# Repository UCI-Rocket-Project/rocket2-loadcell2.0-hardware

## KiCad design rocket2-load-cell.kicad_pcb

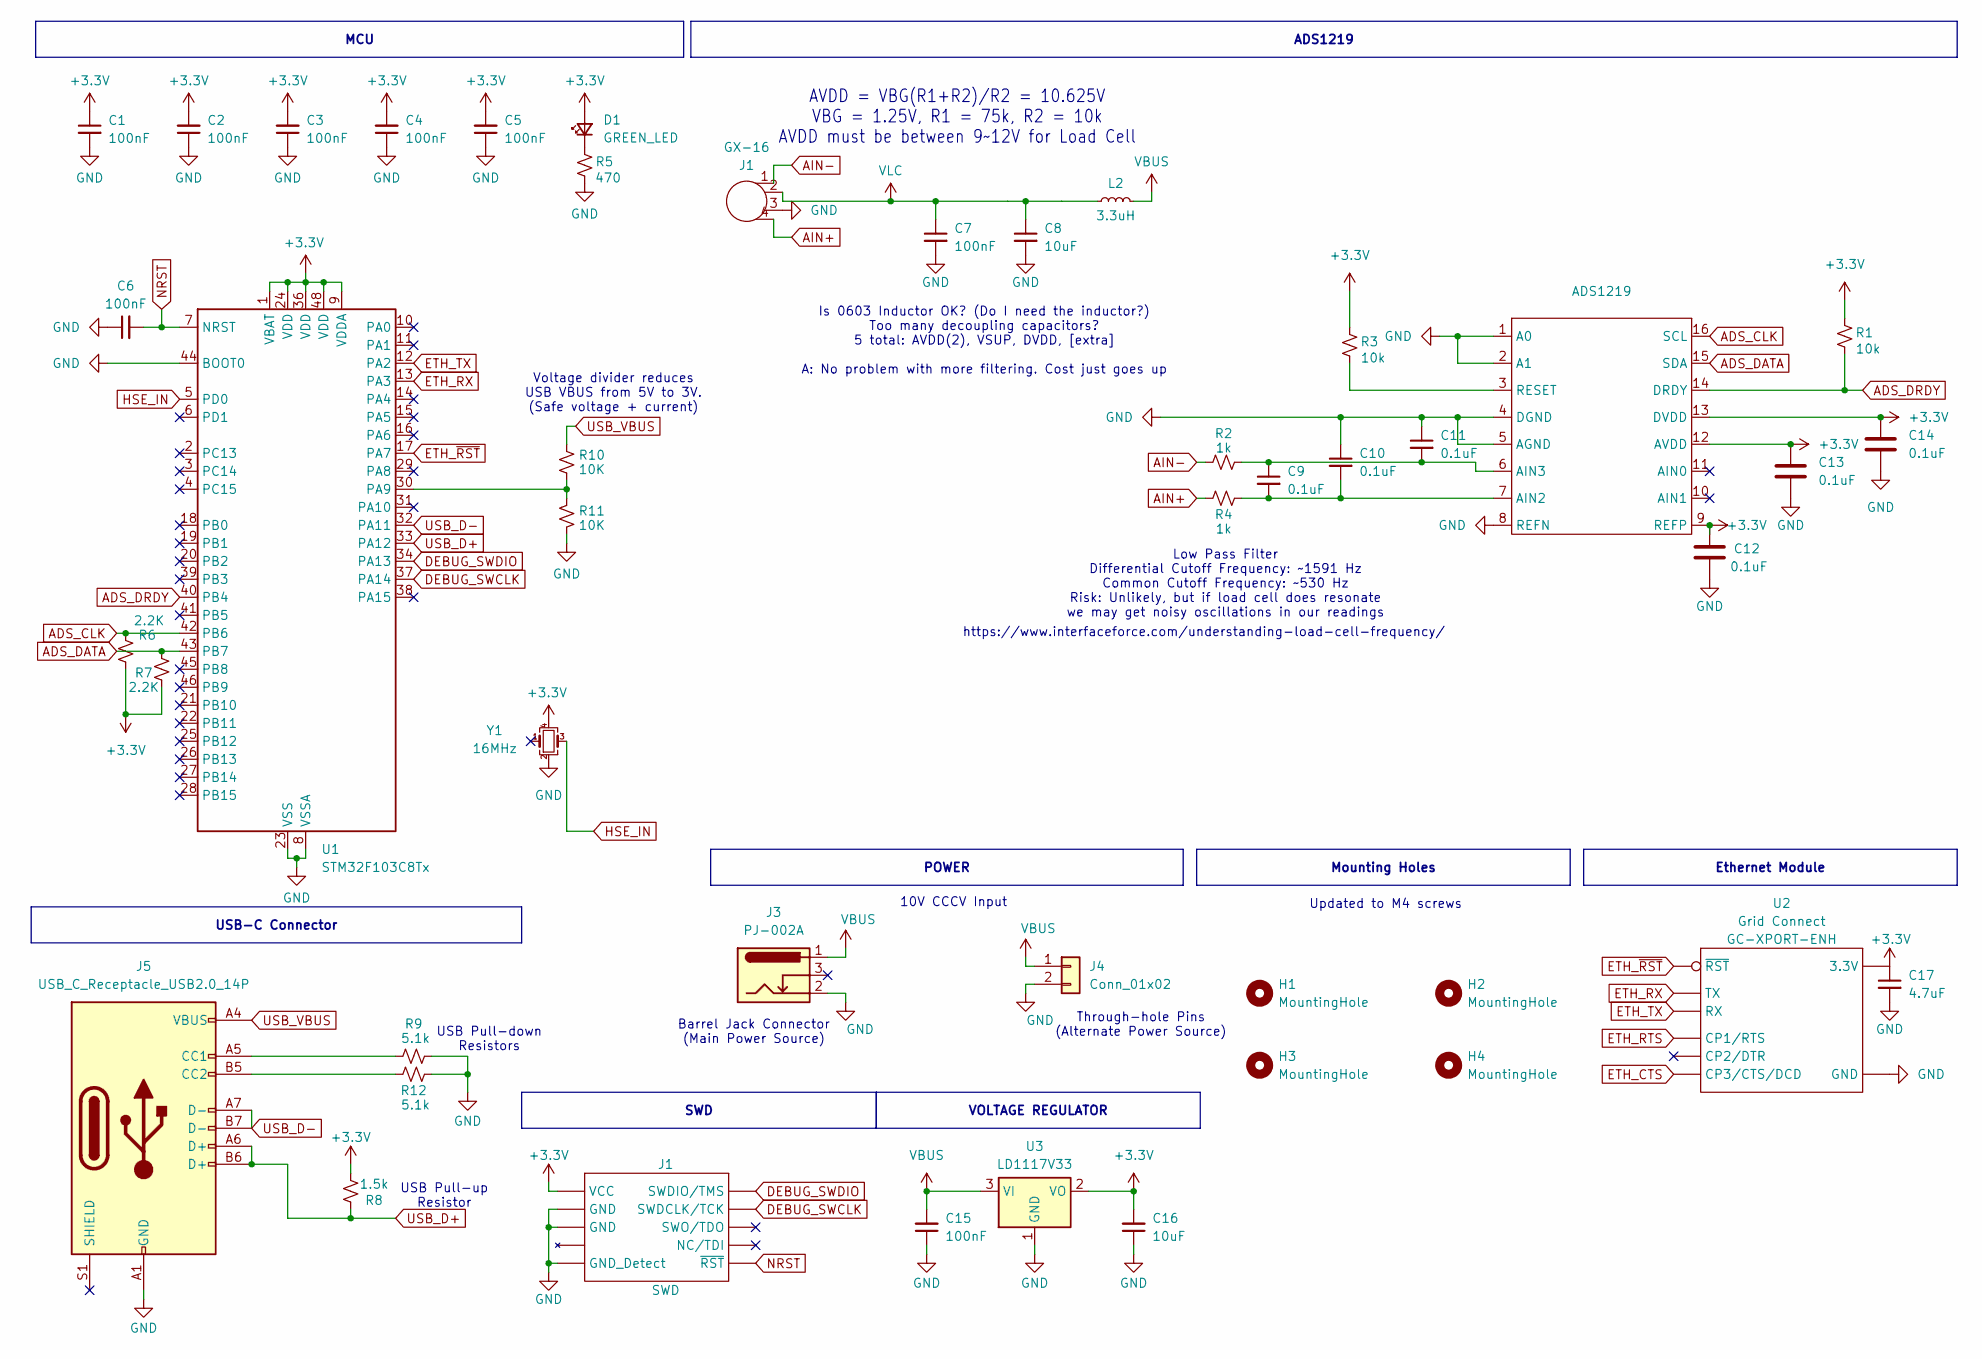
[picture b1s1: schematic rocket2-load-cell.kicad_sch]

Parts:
ADS1219: TSSOP-16_4.4x5mm_P0.65mm
C1, C2, C3, C4, C5, C6, C7, C15: 100nF; C_0603_1608Metric
C8, C16: 10uF; C_0603_1608Metric
C9, C10, C11, C14: 0.1uF; C_0603_1608Metric
C12, C13: 0.1uF; C_0603_1608Metric_Pad1.08x0.95mm_HandSolder
C17: 4.7uF; C_0603_1608Metric; Part # Generic 4.7uF 6.3V X7R 0603 MLCC
D1: GREEN_LED; LED_0603_1608Metric
GX-16: J1; GX16-4
H1, H2, H3, H4: MountingHole; MountingHole_4.3mm_M4_ISO7380_Pad
J1: SWD; PinHeader_2x05_P1.27mm_Vertical_SMD; Part # Generic 2x05 P1.27mm Vertical Pin Heade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
J3: PJ-002A; CUI_PJ-202A
J4: Conn_01x02
J5: USB_C_Receptacle_USB2.0_14P; USB_C_Receptacle_GCT_USB4110
L2: 3.3uH; L_0603_1608Metric
R1, R3: 10k; R_0603_1608Metric
R2, R4: 1k; R_0603_1608Metric
R5: 470; R_0603_1608Metric
R6, R7: 2.2K; R_0603_1608Metric
R8: 1.5k; R_0603_1608Metric
R9, R12: 5.1k; R_0603_1608Metric
R10, R11: 10K; R_0603_1608Metric
U1: STM32F103C8Tx; LQFP-48_7x7mm_P0.5mm
U2: GC-XPORT; Part # GC-XPORT-ENH
U3: LD1117V33; SOT-223-3_TabPin2
Y1: 16MHz; Crystal_SMD_2520-4Pin_2.5x2.0mm; Part # ECS-1633-160-BN-TR

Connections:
+3.3V: ADS1219.9 (REFP), ADS1219.12 (AVDD), ADS1219.13 (DVDD), C1.1, C2.2, C3.2, C4.2, C5.2, C12.1, C13.1, C14.1, C16.2, C17.1, D1.2 (A), J1.1 (VCC), R1.2, R3.2, R6.2, R7.1, R8.1, U1.1 (VBAT), U1.9 (VDDA), U1.24 (VDD), U1.36 (VDD), U1.48 (VDD), U2.2 (3.3V), U3.2 (VO), Y1.4
ADS_CLK: ADS1219.16 (SCL), R6.1, U1.42 (PB6)
ADS_DATA: ADS1219.15 (SDA), R7.2, U1.43 (PB7)
ADS_DRDY: ADS1219.14 (DRDY), R1.1, U1.40 (PB4)
AIN+: GX-16.4, R4.1
AIN-: GX-16.1, R2.1
DEBUG_SWCLK: J1.4 (SWDCLK/TCK), U1.37 (PA14)
DEBUG_SWDIO: J1.2 (SWDIO/TMS), U1.34 (PA13)
ETH_CTS: U2.8 (CP3/CTS/DCD)
ETH_RTS: U2.6 (CP1/RTS)
ETH_RX: U1.13 (PA3), U2.4 (TX)
ETH_TX: U1.12 (PA2), U2.5 (RX)
ETH_~RST: U1.17 (PA7), U2.3 (~RST)
GND: ADS1219.1 (A0), ADS1219.2 (A1), ADS1219.4 (DGND), ADS1219.5 (AGND), ADS1219.8 (REFN), C1.2, C2.1, C3.1, C4.1, C5.1, C6.1, C7.2, C8.2, C10.1, C11.1, C12.2, C13.2, C14.2, C15.1, C16.1, C17.2, GX-16.3, J1.3 (GND), J1.5 (GND), J1.9 (GND_Detect), J3.2, J4.2, J5.A1 (GND), J5.A12 (GND), J5.B1 (GND), J5.B12 (GND), R5.1, R9.2, R11.1, R12.2, U1.8 (VSSA), U1.23 (VSS), U1.35 (VSS), U1.44 (BOOT0), U1.47 (VSS), U2.1 (GND), U3.1 (GND), Y1.2
HSE_IN: U1.5 (PD0), Y1.3
NRST: C6.2, J1.10 (~RST), U1.7 (NRST)
unnamed: ADS1219.7 (AIN2), C9.2, C10.2, R4.2
unnamed: ADS1219.6 (AIN3), C9.1, C11.2, R2.2
unnamed: ADS1219.3 (RESET), R3.1
unnamed: D1.1 (K), R5.2
unnamed: J5.A5 (CC1), R9.1
unnamed: J5.B5 (CC2), R12.1
unnamed: R10.1, R11.2, U1.30 (PA9)
USB_D+: J5.A6 (D+), J5.B6 (D+), R8.2, U1.33 (PA12)
USB_D-: J5.A7 (D-), J5.B7 (D-), U1.32 (PA11)
USB_VBUS: J5.A4 (VBUS), J5.A9 (VBUS), J5.B4 (VBUS), J5.B9 (VBUS), R10.2
VBUS: C15.2, J3.1, J4.1, L2.2, U3.3 (VI)
VLC: C7.1, C8.1, GX-16.2, L2.1

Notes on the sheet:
Voltage divider reduces USB VBUS from 5V to 3V. (Safe voltage + current)
Updated to M4 screws
AVDD = VBG(R1+R2)/R2 = 10.625V VBG = 1.25V, R1 = 75k, R2 = 10k AVDD must be between 9~12V for Load Cell
Low Pass Filter Differential Cutoff Frequency: ~1591 Hz Common Cutoff Frequency: ~530 Hz Risk: Unlikely, but if load cell does resonate we may get noisy oscillations in our readings
USB Pull-down Resistors
Through-hole Pins (Alternate Power Source)
USB Pull-up Resistor
Barrel Jack Connector (Main Power Source)
https://www.interfaceforce.com/understanding-load-cell-frequency/
10V CCCV Input
Is 0603 Inductor OK? (Do I need the inductor?) Too many decoupling capacitors? 5 total: AVDD(2), VSUP, DVDD, [extra] A: No problem with more filtering. Cost just goes up
USB-C Connector
POWER
VOLTAGE REGULATOR
Mounting Holes
SWD
Ethernet Module
ADS1219
MCU

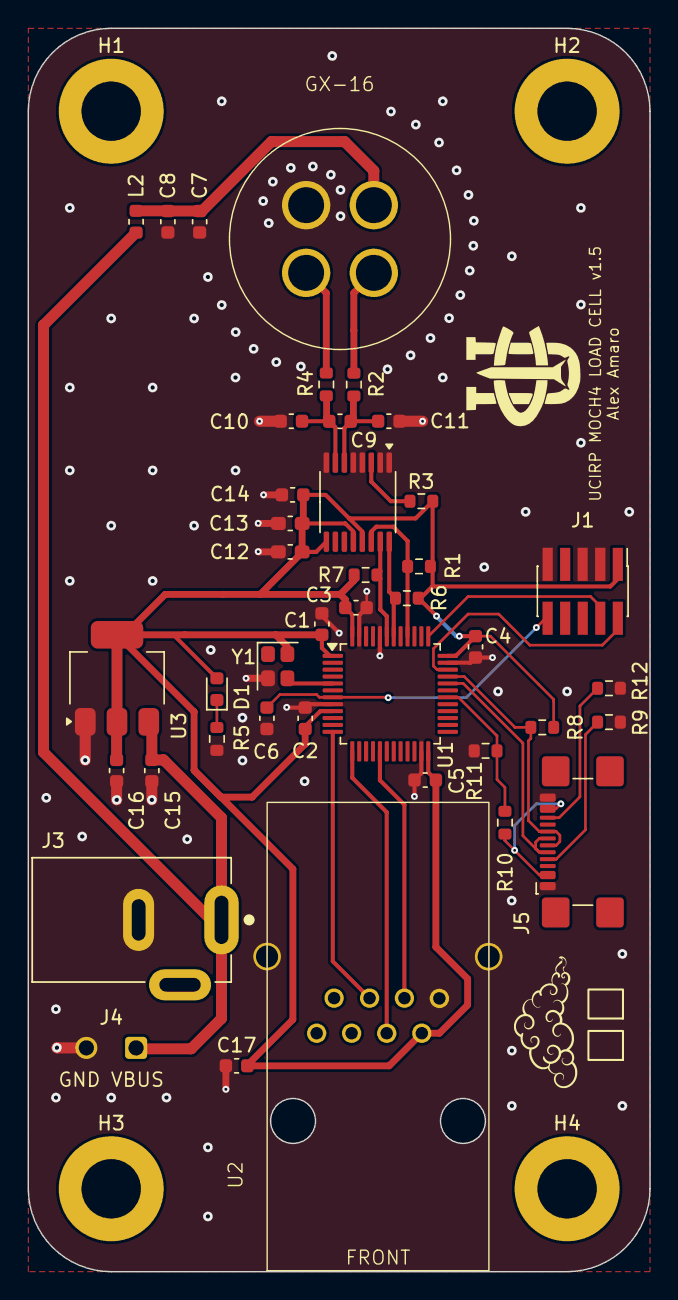
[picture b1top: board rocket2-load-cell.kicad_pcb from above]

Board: 2 copper layers, 45.0 x 90.0 mm, 45 parts (0 on the bottom side), 26 nets.

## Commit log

2025-08-18 1.0 Hardware
    All the hardware from v1.0
2025-08-30 Minor Schematic Fixes
    >> TX and RX lines now connected to their respective opposites (e.g. TX -> RX)
    >> Changed connector to new standard based on the new load cell
    >> Added datasheets to all schematic symbols
2025-09-09 Added USB-B and Filtering
    Replaced memory w/ USB-B connector and strengthened passive RC filtering for differential analog inputs to ADC.
2025-09-19 PCB Updates + Schematic Adjustments
    Layout, signal lines, and basis for power routing.
    Added a voltage divider to the USB_VBUS pin to protect GPIO.
2025-09-19 Adjustments to Decaps
    More direct GND access
2025-09-20 Power Routing Updates
    W.I.P.
2025-09-23 W.I.P. PCB adjustments
    Reducing e-footprint and signal line length to ADC - also corrected some previous issues with signal + power routing
2025-09-24 complete power + signal routing
    fixed bends, shortened length from MCU -> ADC -> Load Cell
2025-09-24 Barrel Jack, New Regulator, and Full Routing
2025-09-24 Library updates
    New footprints for barrel jack and regulator
2025-09-25 Updated based on DRC
    Filled zones filled
2025-09-28 Added Through-hole Backup Power
    Redundancy for the barrel jack
2025-09-30 Final Updates
    Adjusted GX16, reduced E-footprint
2025-10-12 Layout adjustments
    Layout revisions based on CDR feedback
2025-10-12 Updated GX-16 Footprint based on UCIRP Library
2025-10-12 Added fabrication file (ready to order)
2025-10-14 Final Revisions pt. 2
    Final PCB layout revisions (and a few schematic changes) from Robert (Added USB-C, removed excess vias, etc.)
2025-10-14 Final Fix: ADC Layout
    Corrected ADC Layout (Schematic was accidentally mirrored)
2025-10-15 Final Adjustment: SWD Power
    Hooked up power after adjusting layout
2025-10-15 Added BOM File
    :]
2025-11-17 LC v1.5 Fixes (Pt. 1)
    Fixes shorts, pin configurations, among other vital details
2025-11-18 LC v1.5 Fixes (Pt. 2)
    Corrected GX-16 footprint, removed vias from ADC, adjusted decap power line routing, and matched length more for ADS_CLK and ADS_DATA
2025-11-18 GX-16 Update
2025-11-18 LC v1.5 Fixes (Pt. 3)
    Adjusted 10V power line path and filtering on 10V power line near GX connector
2025-11-18 Revisions from review. DO NOT USE. please use this as reference since the traces aren't ideal. There are 2 violations (silkscreen clipping) which can easily be fixed and no errors. if you have any mo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
2025-11-18 Revised GX port rec
2025-11-18 cleaned up more with david (w message)
2025-11-19 LC v1.5 (Pt. 4)
    Final routing changes
2025-11-19 LC v1.5 Final Fix
    Last Routing Patch for Whole Board
